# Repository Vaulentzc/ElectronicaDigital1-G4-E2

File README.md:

# ElectronicaDigital1-laboratorio1
Desarrollo de la práctica 1 de laboratorio sobre la comparación de tecnologías TTL y CMOS

## Introducción
El propósito de este laboratorio fue estudiar y comparar las características de dos tecnologías de circuitos integrados: TTL (Transistor-Transistor Logic) y CMOS (Complementary Metal-Oxide-Semiconductor), a través de dispositivos específicos (74LS04 y CD4069). Se analizaron sus especificaciones eléctricas, se diseñaron circuitos de prueba y se evaluaron parámetros clave como niveles lógicos, tiempos de propagación, disipación de potencia, fan-in, fan-out y sensibilidad a condiciones experimentales.

Además, se implementaron osciladores en anillo para explorar la viabilidad de cada tecnología en aplicaciones prácticas y contrastar su comportamiento en términos de frecuencia de oscilación y forma de onda. Este estudio permite comprender las ventajas y limitaciones de ambas tecnologías, guiando la selección adecuada según los requerimientos de diseño.

## Procedimiento
### Parte 1
  1. Se revisaron los datasheets de los dispositivos 74LS04 y CD4069 proporcionados por el fabricante. Se identificaron y registraron los parámetros relevantes como V<sub>IH</sub>, V<sub>IL</sub>, V<sub>OH</sub>, V<sub>OL</sub>, t<sub>PHL</sub>, t<sub>PLH</sub>​, entre otros, para realizar una comparación directa. 
  
  2. Se analizaron los esquemas de aplicación recomendados en los datasheets para identificar los circuitos equivalentes típicos.
  
  3. Se implementó un circuito de prueba para cada dispositivo en el que se aplicó una señal cuadrada de 1 kHz con una amplitud adecuada. Utilizando un osciloscopio, generador de señales y una fuente DC con VCC= 5V,se midieron los niveles de V<sub>OUT</sub> en función de V<sub>IN</sub> para obtener la función de transferencia y determinar   V<sub>IH</sub>, V<sub>IL</sub>, V<sub>OH</sub>, V<sub>OL</sub>.
  
### Parte 2
  1. Se determinó el fan-in y fan-out de cada uno de los dispositivos; el fan-in consiste en el número de entradas mientras que el fan-out se determinó con midiendo la relación entre las corrientes de entrada y salida con cada uno de los dispositivos.
  2. Se calculó la disipación de potencia.
  3. Se realizó la implementación de un circuito de entrada y de salida para que fuera funcional tanto para el TTL como para el CMOS teniendo en cuenta los parámetros encontrados en la sección anterior para analizar el comportamiento del mismo.

### Parte 3
En esta última parte se planteó estudiar el oscilador en anillo basado en la compuerta NOT. Para ello se realizó el montaje de dos osciladores en anillo con el negador CMOS, por facilidad se escogió hacerlos con 3 y con 5 entradas.
 En base a esto, se realizó la lectura de su frecuencia de oscilación y de la forma de su onda, para luego hacer una comparación entre ambos osciladores según lo observado.

## Resultados y análisis

### Parte 1
#### 1. Comparación de los datasheets.

Al comparar las especificaciones de los dos dispositivos que se encuentran en los datasheets se pudo determinar

El de tecnología CMOS, tiene un consumo de corriente extremadamente bajo cuando las entradas están en un estado estable, ya que los transistores CMOS consumen corriente principalmente durante las transiciones. En contraste, el 74LS04, al ser de tecnología TTL, consume corriente constantemente debido a la polarización activa de los transistores bipolares. Entonces el CD4069 es mucho más eficiente en cuanto a consumo energético para aplicaciones de bajo consumo
  
  De la misma manera el CD4069 tiene un rango de voltaje de alimentación más amplio (3 V a 15 V) mientras que el 74LS04 opera en un rango más limitado (4.75 V y 5.25 V). Esto hace que el CD4069 sea más versátil en aplicaciones con diferentes niveles de alimentación o baterías. Además, la tecnología CMOS puede operar en un rango de temperatura más amplio (-55°C a 125°C) en comparación con el rango típico del 74LS04 (-40°C a 85°C) lo que permite que el CD4069 tenga una gama más grande de aplicaciones.
  
  Por otro lado, el 74LS04 tiene tiempos de propagación mucho más cortos que el CD4069, gracias a la tecnología TTL, que está optimizada para altas velocidades. El tiempo de propagación del 74LS04 es de aproximadamente 10 ns, mientras que el CD4069 tiene tiempos de propagación en el rango de 50 ns a 200 ns, dependiendo del voltaje de alimentación. Esto hace que el 74LS04 sea más adecuado para aplicaciones de alta frecuencia donde la velocidad es crítica. También es más compatible con otros circuitos TTL sin necesidad de ajustes de niveles, mientras que el CMOS requiere atención especial para la compatibilidad con niveles lógicos TTL/CMOS.
       
  Si nos centramos en los niveles lógicos de entrada el 74LS04 tiene niveles lógicos específicos para tecnología TTL, mientras que el CD4069 ajusta sus niveles en función de la alimentación (Vcc). Esto hace que el CMOS sea más flexible en diferentes entornos de voltaje. En términos de salida, el CD4069 tiene valores más cercanos a los límites de Vcc (VOH y VOL), lo que lo hace ideal para aplicaciones digitales puras.
  
  También se considera que el 74LS04 consume más corriente en sus entradas y salidas, mientras que el CD4069 tiene una corriente de entrada casi nula, ideal para circuitos de bajo consumo. Se puede decir que las corrientes de salida también reflejan que el 74LS04 está diseñado para manejar mayores cargas.
  
  En cuanto a tiempos de propagación, el TTL es significativamente más rápido, lo que lo hace más adecuado para aplicaciones que requieren alta velocidad.Mientras que el CMOS al ser más lento, es más adecuado para aplicaciones de baja frecuencia o señales analógicas.
    
Por último,  el CD4069 tiene márgenes más amplios entre los niveles de entrada válidos y los niveles de salida válidos, lo que lo hace más tolerante al ruido en las señales.

#### 2. Circuitos equivalentes

Los circuitos equivalentes del 74LS04 (TTL) y el CD4069 (CMOS) representan cómo están diseñadas internamente las compuertas NOT en cada dispositivo.
El circuito equivalente del TTL es el siguiente:
[Parte1/Datasheets/Circuito equivalente-TTL 74LS04.png](https://github.com/Vaulentzc/ElectronicaDigital1-laboratorio1/blob/ecb55ed399cde78d55f891e655c1c9d768b6fda7/Parte1/Datasheets/Circuito%20equivalente-TTL%2074LS04.png))

El circuito equivalente del CMOS es el siguiente:
([Parte1/Datasheets/Circuito equivalenteCMOS-CD4049.png](https://github.com/Vaulentzc/ElectronicaDigital1-laboratorio1/blob/bd185773e0bfe6394d03626681a8b66140edc500/Parte1/Datasheets/Circuito%20equivalenteCMOS-CD4049.png))

#### 3. Montaje y simulaciones
  Aplicando una señal cuadrada con una frecuencia de 1 KHz se obtuvieron los siguientes resultados, tanto en la simulaciones como en la práctica que se pueden contrastar con los teóricos.

##### TTL 74LS04
Se puede observar la simulación implementada
)

A partir de ello se obtuvieron las siguientes medidas
([Parte1/Resultados parte1/TablaResultadosTTL.png](https://github.com/Vaulentzc/ElectronicaDigital1-laboratorio1/blob/bd185773e0bfe6394d03626681a8b66140edc500/Parte1/Resultados%20parte1/TablaResultadosTTL%20.png))

   El circuito TTL 74LS04 presenta un buen desempeño en términos de niveles altos de voltaje (V<sub>OH</sub>​), pero tiene problemas con los niveles bajos (V<sub>IL</sub> y V<sub>OL</sub>), lo cual podría generar inconsistencias lógicas. Además, los tiempos de respuesta son considerablemente más lentos que los valores teóricos, especialmente en la práctica, indicando limitaciones en la velocidad del dispositivo y condiciones experimentales.

Aunque si se considera el circuito implementado las resistencias introducen retardos, distorsionan las señales cuadradas y afectan las mediciones de voltaje lógico. Por lo tanto se podría haber probado con valores mucho menores de resistencias para obtener resultados más adecuados. En la entrada Afecta la corriente de entrada, causando un incremento en V<sub>IL</sub>​ y posibles problemas en la interpretación de niveles bajos. En la salida, aumenta V<sub>OL</sub> e incrementa los tiempos de subida (tr) y bajada (tf), y los de propagación por el efecto RC.

 ##### CMOS CD4069
Se puede observar la simulación implementada
([Parte1/Fotos de las simulaciones- Parte1/SimCMOS.png](https://github.com/Vaulentzc/ElectronicaDigital1-laboratorio1/blob/bd185773e0bfe6394d03626681a8b66140edc500/Parte1/Fotos%20de%20las%20simulaciones-%20Parte1/SimCMOS.png))

A partir de ello se obtuvieron las siguientes medidas
([Parte1/Resultados parte1/TablaResultadosCMOS.png](https://github.com/Vaulentzc/ElectronicaDigital1-laboratorio1/blob/bd185773e0bfe6394d03626681a8b66140edc500/Parte1/Resultados%20parte1/TablaResultadosCMOS.png))

Al analizar los datos de entrada, los valores medidos en práctica y simulación son muy inferiores a los valores teóricos.
Esto se debe a que el CMOS es muy sensible a la impedancia en la entrada. Al colocar una resistencia de 10 kΩ, se limita la corriente que puede cargar la capacitancia de la puerta de entrada, lo cual altera los niveles de voltaje, por lo que no está obteniendo los valores lógicos requeridos.

En cuanto a la salida,el V<sub>OH</sub> es relativamente cercano al valor teórico (4.95V a 4.64V), por lo que las tecnologías CMOS tienen baja corriente de salida. En cuanto a los tiempos de subida, bajada y propagación que son mucho mayores a los teóricos puede ser debido a la constante de tiempo RC causada por las resistencias de 10 kΩ y la capacitancia parásita del circuito

#### ---

 En los resultados se observa que el CMOS es más sensible a las resistencias que el TTL, debido a la alta impedancia de entrada y baja capacidad de corriente en la salida. Aunque el TTL estuvo más próximo a los valores teóricos, ambos negadores fueron afectados por las condiciones experimentales y los altos valores en las resistencias.
 
### Parte 2
#### 1. Fan-in y Fan-out

El fan-in define la cantidad de entradas lógicas que puede manejar una puerta. En este caso, tanto en TTL 74LS04 como en CMOS CD4069, cada puerta lógica tiene 1 entrada por puerta inversora, por lo que el fan-in para ambos es 1.

El fan-out define cuántas puertas lógicas de la misma tecnología pueden ser controladas (alimentadas) por la salida de una sola puerta lógica. Para ello,se aplica una fórmula que relaciona la corriente máxima que una compuerta puede suministrar sin que su salida se distorsione con la corriente requerida por una unidad de carga.

  ##### TTL 74LS04
En primer lugar, para los cálculos teóricos se utilizaron los datos proporcionados en el datasheet
del fabricante:
  ###### Estado lógico alto.
La corriente máxima de salida (IOH) es de 0,4 mA, mientras que la corriente requerida de entrada por una carga (IIH) es de 20 μA. Usando la expresión: Fan-out.alto = IOH/IIH = 20

Por lo tanto, el fan-out en estado lógico alto es 20.

  ###### Estado lógico bajo.
En este caso, se consideran IOL y IIL, con valores de 8 mA y 0,4 mA respectivamente. Usando la expresión Fan-out.bajo = IOL/IIL = 20
El fan-out en estado lógico bajo también es 20.

En conclusión, el inversor 74LS04 tiene un fan-out teórico de 20 en ambos estados.

###### Simulación.
En esta etapa se realizó una simulación para verificar este valor, conectando diferentes n ´umeros de unidades de carga a la salida del inversor y midiendo la corriente requerida en cada configuración:

Con dicha simulación se midieron los valores en estado lógico alto y bajo para que al al final se recopile el menor valor.
([Parte2/Fotos de las simulaciones-Parte2/SimFanOutTTL.png](https://github.com/Vaulentzc/ElectronicaDigital1-laboratorio1/blob/bd185773e0bfe6394d03626681a8b66140edc500/Parte2/Fotos%20de%20las%20simulaciones-Parte2/SimFanOutTTL.png))

  ##### CMOS CD4069
  Al igual que con el TTL, para los cálculos teóricos se utilizaron los datos proporcionados en el datasheet
del fabricante:

  ###### Estado lógico alto.
La corriente máxima de salida (IOH) es de -0,52 mA pero se toma el valor absoluto, mientras que la corriente requerida de entrada por una carga (IIH) es de 0.01 μA. Usando la expresión: Fan-out.alto = IOH/IIH = 52 que se puede tomar como 50

Por lo tanto, el fan-out en estado lógico alto es 50.

  ###### Estado lógico bajo.
En este caso, los valores de IOL e IIL para CMOS suelen ser muy pequeños, por lo que tienden a tomarse como iguales a los del estado lógico alto. En conclusión, el inversor CD4069 tiene un fan-out teórico de aproximadamente 50 en ambos estados.

###### Simulación.
En esta etapa se realizó una simulación para verificar este valor, se realizó la misma simulación que para el TTL:
([Parte2/Fotos de las simulaciones-Parte2/SimFanOutCMOS.png](https://github.com/Vaulentzc/ElectronicaDigital1-laboratorio1/blob/bd185773e0bfe6394d03626681a8b66140edc500/Parte2/Fotos%20de%20las%20simulaciones-Parte2/SimFanOutCMOS.png))

Con lo que se obtuvieron los siguientes valores

En teoría, CMOS debería tener un fan-out mucho mayor que el TTL, debido a sus menores corrientes de entrada. Sin embargo, los resultados experimentales muestran un fan-out similar en ambos dispositivos aunque se mantiene la relación de que el fan-out del CMOS sea mayor. Lo cual indica que en las condiciones del experimento y la simulación, las corrientes medidas en CMOS fueron significativamente mayores a las esperadas, lo cual sugiere problemas relacionados con el circuito, la medición o las condiciones de carga. Esto resalta la importancia de considerar las condiciones de prueba y el impacto de factores externos al comparar dispositivos digitales.

#### 2. Disipación de potencia.
Debido a la incongruencia obtenida en el Fan-out experimental, la disipación de potencia también cuenta con resultados que no concuerdan con el comportamiento teórico por los mismos factores que se mencionaron anteriormente.

  ##### TTL 74LS04

  ##### CMOS CD4069

#### 3. Implementación circuito funcional para CMOS y TTL.
En el siguiente video se puede observar el funcionamiento del circuito propuesto de entrada y de salida para que fuera funcional tanto para el TTL como para el CMOS teniendo en cuenta los parámetros encontrados en la sección anterior para analizar el comportamiento del mismo.

([Parte2/Fotos practica-parte2/Circuito Propuesto.jpeg](https://github.com/Vaulentzc/ElectronicaDigital1-laboratorio1/blob/bd185773e0bfe6394d03626681a8b66140edc500/Parte2/Fotos%20practica-parte2/Video%20Circuito.mp4))

### Parte 3
Para esta última etapa se realizaron las simulaciones de un oscilador en anillo de 3 estpas y otro de 5 etapas implementando un CMOS dado a que como se mencionó anteriormente es generalmente más eficiente, versátil y adecuado para aplicaciones modernas que priorizan el bajo consumo de energía y la flexibilidad en el diseño por lo que serán más visibles las etapas.

Simulación del oscilador en anillo con 3 etapas en CMOS con el que se obtuvo una frecuencia de 1.718 MHz 
([Parte3/Fotos de las simulaciones-Parte3/OsciladorCMOS-con3.png](https://github.com/Vaulentzc/ElectronicaDigital1-laboratorio1/blob/bd185773e0bfe6394d03626681a8b66140edc500/Parte3/Fotos%20de%20las%20simulaciones-Parte3/OsciladorCMOS-con3.png))

Simulación del oscilador en anillo con 5 etapas en CMOS con el que se obtuvo una frecuencia de 0.7689 MHz
([Parte3/Fotos de las simulaciones-Parte3/OsciladorCMOS-con5.png](https://github.com/Vaulentzc/ElectronicaDigital1-laboratorio1/blob/bd185773e0bfe6394d03626681a8b66140edc500/Parte3/Fotos%20de%20las%20simulaciones-Parte3/OsciladorCMOS-con5.png))

Posterior a ello se dispuso a hacer el montaje experimental de ambos osciladores obteniendo los siguientes resultados

Oscilador en anillo experimental con 3 etapas en CMOS con el que se obtuvo una frecuencia de 3.50 MHz
([Parte3/Fotos practica-parte3/5gates.jpeg](https://github.com/Vaulentzc/ElectronicaDigital1-laboratorio1/blob/bd185773e0bfe6394d03626681a8b66140edc500/Parte3/Fotos%20practica-parte3/5gates.jpeg))

Oscilador en anillo experimental con 5 etapas en CMOS con el que se obtuvo una frecuencia de 2.13 MHz
([Parte3/Fotos practica-parte3/3gates.jpeg](https://github.com/Vaulentzc/ElectronicaDigital1-laboratorio1/blob/bd185773e0bfe6394d03626681a8b66140edc500/Parte3/Fotos%20practica-parte3/3gates.jpeg))

La frecuencia de oscilación está inversamente relacionada con el número de etapas en el oscilador. Es decir, a mayor número de etapas, mayor será el tiempo total de propagación del circuito, lo que lleva a una frecuencia más baja. Esto ocurre porque cada etapa introduce un retardo debido a la conmutación de la puerta negadora, y el tiempo total de propagación se acumula a medida que aumenta el número de etapas. Por lo tanto un oscilador con tres etapas tendrá un tiempo de propagación más bajo y con ello, una frecuencia más alta, y un oscilador con 5 etapas tendrá un tiempo de propagación más alto y una frecuencia más baja.

## Conclusiones
1. Los dispositivos CMOS (CD4069) demostraron ser más eficientes en términos de consumo energético, mayor rango de voltaje de operación y mejor tolerancia al ruido. Estas características los hacen ideales para aplicaciones de bajo consumo y entornos variados.
   
2. Por otro lado, los dispositivos TTL (74LS04) ofrecen tiempos de propagación significativamente menores, lo que los hace más adecuados para aplicaciones de alta velocidad o con requisitos estrictos de compatibilidad lógica. Sin embargo, consumen más energía y tienen un rango de operación más limitado.
   
3. En teoría, los dispositivos CMOS presentan un fan-out mayor debido a sus bajas corrientes de entrada y salida. Sin embargo, los resultados experimentales indicaron valores similares para ambos dispositivos, probablemente debido a factores externos como la impedancia de carga y condiciones de medición. Esto subraya la importancia de optimizar las condiciones experimentales para reflejar mejor el comportamiento teórico.
   
4. La frecuencia de oscilación en los osciladores en anillo está inversamente relacionada con el número de etapas, como se observó tanto en las simulaciones como en los resultados experimentales. Los osciladores con tecnología CMOS ofrecieron una implementación más eficiente en términos de consumo de energía, aunque con una sensibilidad mayor a las condiciones externas.
   
5. Tanto los dispositivos TTL como CMOS mostraron desviaciones respecto a los valores teóricos debido a factores como el uso de resistencias altas y la influencia de impedancias no ideales. Esto resalta la necesidad de considerar en próximos laboratorios la configuración del circuito para obtener resultados precisos y reproducibles.
   
6. La elección entre TTL y CMOS debe basarse en las necesidades específicas de la aplicación. Para sistemas que priorizan la velocidad y compatibilidad, TTL es una opción adecuada. Para aplicaciones de bajo consumo energético y alta flexibilidad, CMOS es preferible.

## Referencias
-Uelectronics.DataSheet TTL 74LS04(https://uelectronics.com/producto/cd4049be-inversor-hexadecima-dip-16/)

-Uelectronics.Datasheet CMOS CD4069(https://uelectronics.com/producto/74ls04-compuerta-not-sn74ls04n/?srsltid=AfmBOopSNMqnw9-t7gDojXjZ6zj2RbfQPI2q1okUrkqvsDHkUBCRXMIU)

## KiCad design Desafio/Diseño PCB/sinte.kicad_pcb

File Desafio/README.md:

# SynthIce: Sintetizador digital basado en FPGA

## Descripción
SynthIce es un sintetizador digital desarrollado sobre la FPGA BlackIce40, utilizando Verilog. Permite la síntesis y modulación de sonido en tiempo real, ofreciendo una herramienta educativa y accesible para la exploración de conceptos de síntesis digital de audio.

## Características principales
- Generación de notas musicales mediante pulsadores (C4 a B4, incluyendo semitonos).
- Modulador de frecuencia controlado por encoder rotativo.
- Reproducción de pistas almacenadas en memoria con ajuste dinámico de BPM.
- Conversión digital-análoga y amplificación para salida de audio.
- Diseño modular en Verilog, optimizado para implementación en FPGA.

## Requerimientos de Hardware
- FPGA BlackIce40.
- 5 pulsadores para la entrada de notas.
- Encoder rotativo para modulación.
- Encoder rotativo para ajuste de BPM.
- Amplificador PAM8403.
- Parlantes de 8W.
- Alimentación de 5V vía USB Micro.

## Futuras Mejoras
- Integración con MIDI para control externo.
- Implementación de más formas de onda (sinusoidal, triangular, etc.).
- Optimización del diseño de PCB.
- Expansión de memoria para almacenar múltiples pistas.

# Informe
El informe que contiene el registro del desarrollo de SynthIce está adjunto en el repositorio donde se encuentra la descripción detallada de cada módulo tanto en eñ planteamiento como en el diseño a través de la metodología Top-down.
[Informe SynthIce](https://github.com/Vaulentzc/ElectronicaDigital1-G4-E2/blob/142babee6b790b45e1a883408abd123a2dc3bb51/Desafio/informe%20SinthIce.pdf)

## Autores
- **Samuel David Sánchez Cárdenas** - [samsanchezca@unal.edu.co](mailto:samsanchezca@unal.edu.co)
- **Dayanna Segovia Arteaga** - [daarteagas@unal.edu.co](mailto:daarteagas@unal.edu.co)
- **Paula Valentina Álvarez Chaparro** - [palvarezch@unal.edu.co](mailto:palvarezch@unal.edu.co)

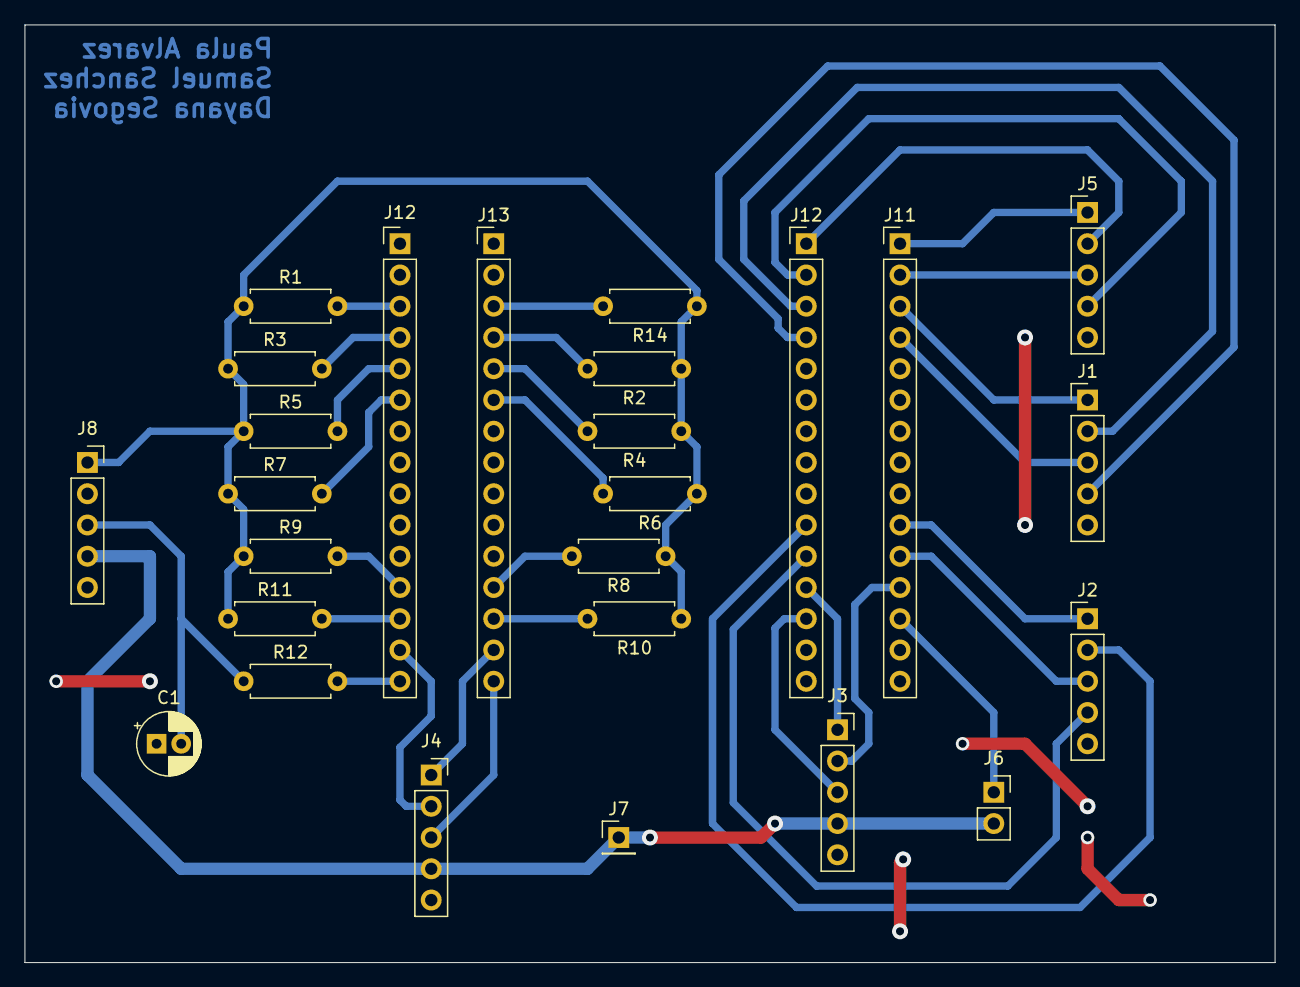
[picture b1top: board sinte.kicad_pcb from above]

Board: 2 copper layers, 101.6 x 76.2 mm, 26 parts (0 on the bottom side), 36 nets.

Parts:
C1: C; CP_Radial_D5.0mm_P2.00mm
J1: Botones2; PinHeader_1x05_P2.54mm_Vertical
J2: Botones3; PinHeader_1x05_P2.54mm_Vertical
J3: Encoder notas; PinSocket_1x05_P2.54mm_Vertical
J4: Encoder pistas; PinSocket_1x05_P2.54mm_Vertical
J5: Botones1; PinHeader_1x05_P2.54mm_Vertical
J6: Switch pistas; PinSocket_1x02_P2.54mm_Vertical
J7: FPGA5V; PinHeader_1x01_P2.54mm_Vertical
J8: PAM; PinSocket_1x05_P2.54mm_Vertical
J11: Entradas2; PinHeader_1x15_P2.54mm_Vertical
J12: Entradas1; PinHeader_1x15_P2.54mm_Vertical
J13: Salidas1; PinHeader_1x15_P2.54mm_Vertical
J14: Salidas2; PinHeader_1x15_P2.54mm_Vertical
R1, R2, R3, R4, R5, R6, R7, R8, R9, R10, R11, R12, R14: R; R_Axial_DIN0207_L6.3mm_D2.5mm_P7.62mm_Horizontal

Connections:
+5V: J3.4, J4.4, J6.2, J7.1, J8.4
/9_Do: J13.3, R14.2
/10_Re: J13.4, R2.2
/11_DoS: J14.3, R1.2
/12_ReS: J14.4, R3.2
/15_Mi: J13.5, R4.2
/16_FaS: J13.6, R6.2
/17_Fa: J14.5, R5.2
/18_sol: J14.6, R7.2
/19_La: J2.1, J11.10
/20_si: J2.3, J11.11
/21_SolS: J2.2, J12.10
/22_LaS: J2.4, J12.11
/23_EncocanalB: J3.2, J11.12
/24_on/offpista: J6.1, J11.13
/25_EncocanalA: J3.1, J12.12
/26_EncoSW: J3.3, J12.13
/28_SolS: J13.12, R8.2
/29_LaS: J13.13, R10.2
/31_La: J14.12, R9.2
/32_Si: J14.13, R11.2
/33_pEncocanalA: J4.1, J13.14
/34_pEncoSW: J4.3, J13.15
/37_pEncocanalB: J4.2, J14.14
/38_Pistas: J14.15, R12.2
/49_Mi: J1.2, J12.3
/52_FaS: J1.4, J12.4
/99_Sol: J1.3, J11.4
/101_Fa: J1.1, J11.3
/102_Re: J5.4, J12.2
/104_Do: J5.2, J12.1
/105_ReS: J5.3, J11.2
/106_DoS: J5.1, J11.1
/L_Notas: J8.1, R1.1, R2.1, R3.1, R4.1, R5.1, R6.1, R7.1, R8.1, R9.1, R10.1, R11.1, R14.1
/R_pistas: C1.2, J8.3, R12.1
GND: C1.1, J1.5, J2.5, J3.5, J4.5, J5.5, J8.2, J8.5, J11.15

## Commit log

2024-12-13 Create Parte1
2025-01-16 lab1
2025-01-16 lab2,3
2025-01-23 prueba instalacion repositorio
2025-01-23 eliminación archivos
2025-02-14 code
2025-02-14 Rename Desafio/top.pcf to Desafio/code/top.pcf
2025-02-14 Rename Desafio/Makefile to Desafio/code/Makefile
2025-02-14 Rename Desafio/encoder.dig to Desafio/code/encoder.dig
2025-02-14 Rename Desafio/encoder.v to Desafio/code/encoder.v
2025-02-14 Rename Desafio/encoderB.v to Desafio/code/encoderB.v
2025-02-14 Rename Desafio/encoderMod.v to Desafio/code/encoderMod.v
2025-02-14 Rename Desafio/encoderModB.v to Desafio/code/encoderModB.v
2025-02-14 Rename Desafio/frecDiv.v to Desafio/code/frecDiv.v
2025-02-14 Rename Desafio/frecDivMain.v to Desafio/code/frecDivMain.v
2025-02-14 Rename Desafio/pulsadorNote.v to Desafio/code/pulsadorNote.v
2025-02-14 Rename Desafio/reproductorPista.v to Desafio/code/reproductorPista.v
2025-02-14 Rename Desafio/romContador.dig to Desafio/code/romContador.dig
2025-02-14 Rename Desafio/romContador.v to Desafio/code/romContador.v
2025-02-14 Rename Desafio/sintetizador.v to Desafio/code/sintetizador.v
2025-02-14 Create link video
2025-02-14 Update link video
